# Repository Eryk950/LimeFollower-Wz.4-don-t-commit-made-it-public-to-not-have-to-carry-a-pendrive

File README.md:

Line Follower code
needs AutoPID library by Ryan Downing

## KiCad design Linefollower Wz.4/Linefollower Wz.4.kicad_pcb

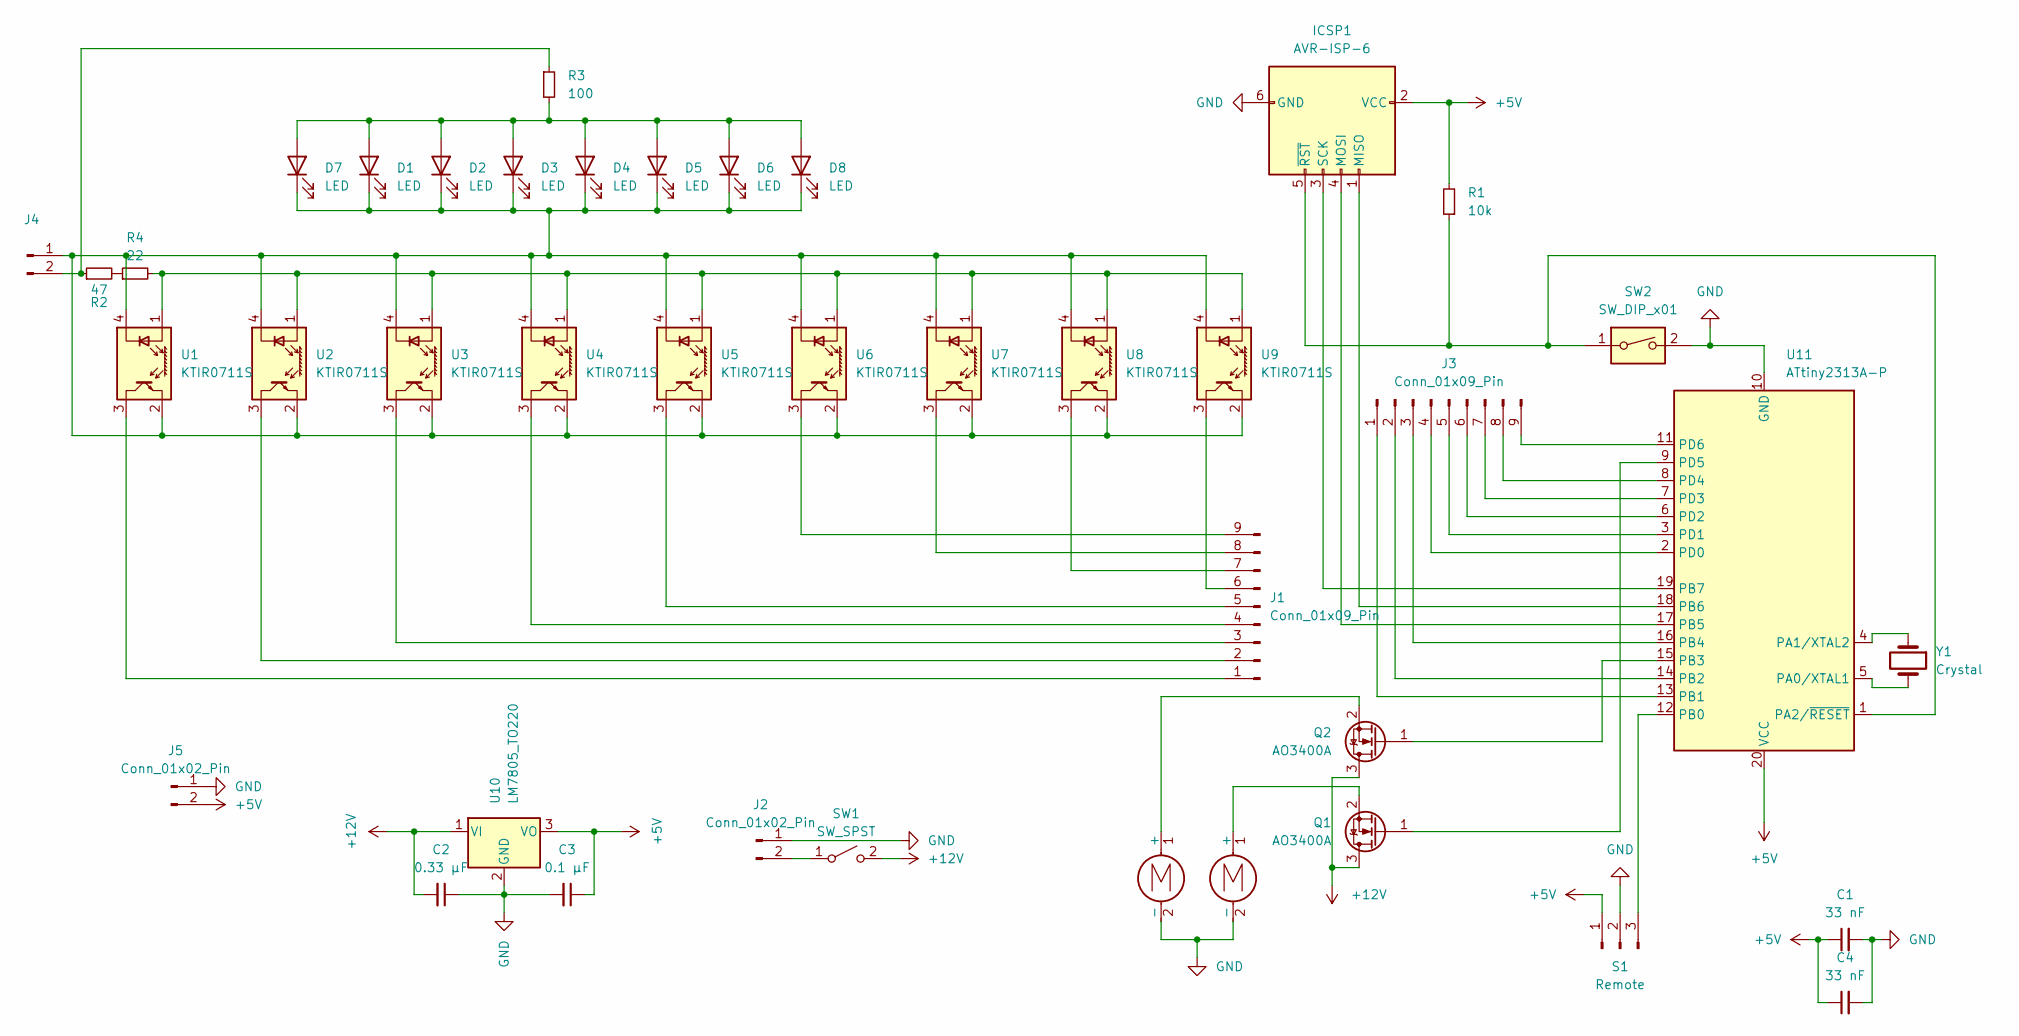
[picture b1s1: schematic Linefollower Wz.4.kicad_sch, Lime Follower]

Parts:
C1, C4: 33 nF; C_Disc_D3.4mm_W2.1mm_P2.50mm
C2: 0.33 µF; C_Disc_D3.4mm_W2.1mm_P2.50mm
C3: 0.1 µF; C_Disc_D3.4mm_W2.1mm_P2.50mm
D1, D2, D3, D4, D5, D6, D7, D8: LED; LED_0805_2012Metric_Pad1.15x1.40mm_HandSolder
ICSP1: AVR-ISP-6; PinHeader_2x03_P2.54mm_Vertical
J1, J3: Conn_01x09_Pin; PinSocket_1x09_P2.54mm_Vertical
J2, J4, J5: Conn_01x02_Pin; PinHeader_1x02_P2.54mm_Vertical
M1, M2: Motor_DC; PinHeader_1x02_P2.54mm_Vertical
Q1, Q2: AO3400A; TO-220-3_Horizontal_TabDown
R1: 10k; R_0805_2012Metric_Pad1.20x1.40mm_HandSolder
R2: 47; R_0805_2012Metric_Pad1.20x1.40mm_HandSolder
R3: 100; R_0805_2012Metric_Pad1.20x1.40mm_HandSolder
R4: 22; R_0805_2012Metric_Pad1.20x1.40mm_HandSolder
S1: Remote; PinSocket_1x03_P2.54mm_Vertical
SW1: SW_SPST; SW_DIP_SPSTx01_Slide_9.78x4.72mm_W7.62mm_P2.54mm
SW2: SW_DIP_x01; SW_PUSH_1P1T_6x3.5mm_H4.3_APEM_MJTP1243
U1, U2, U3, U4, U5, U6, U7, U8, U9: KTIR0711S
U10: LM7805_TO220; TO-220-3_Horizontal_TabDown
U11: ATtiny2313A-P; DIP-20_W7.62mm
Y1: Crystal; Crystal_HC49-U_Vertical

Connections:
+5V: C1.1, C3.1, C4.1, ICSP1.2 (VCC), J5.2, R1.2, S1.1, U10.3 (VO), U11.20 (VCC)
+12V: C2.2, Q1.3 (D), Q2.3 (D), SW1.2 (B), U10.1 (VI)
GND: C1.2, C2.1, C3.2, C4.2, ICSP1.6 (GND), J2.1, J5.1, M1.2 (-), M2.2 (-), S1.2, SW2.2, U10.2 (GND), U11.10 (GND); also elsewhere on the board
unnamed: D1.2 (A), D2.2 (A), D3.2 (A), D4.2 (A), D5.2 (A), D6.2 (A), D7.2 (A), D8.2 (A), R3.2
unnamed: D1.1 (K), D2.1 (K), D3.1 (K), D4.1 (K), D5.1 (K), D6.1 (K), D7.1 (K), D8.1 (K), J4.1, U1.2 (E), U1.4 (K), U2.2 (E), U2.4 (K), U3.2 (E), U3.4 (K), U4.2 (E), U4.4 (K), U5.2 (E), U5.4 (K), U6.2 (E), U6.4 (K), U7.2 (E), U7.4 (K), U8.2 (E), U8.4 (K), U9.2 (E), U9.4 (K)
unnamed: ICSP1.1 (MISO), U11.18 (PB6)
unnamed: ICSP1.4 (MOSI), U11.17 (PB5)
unnamed: ICSP1.3 (SCK), U11.19 (PB7)
unnamed: ICSP1.5 (~RST), R1.1, SW2.1, U11.1 (PA2/~RESET)
unnamed: J1.1, U1.3 (C)
unnamed: J1.2, U2.3 (C)
unnamed: J1.3, U3.3 (C)
unnamed: J1.4, U4.3 (C)
unnamed: J1.5, U5.3 (C)
unnamed: J1.6, U9.3 (C)
unnamed: J1.7, U8.3 (C)
unnamed: J1.8, U7.3 (C)
unnamed: J1.9, U6.3 (C)
unnamed 18: J2.2, SW1.1 (A); also elsewhere on the board
unnamed: J3.1, U11.13 (PB1)
unnamed: J3.2, U11.14 (PB2)
unnamed: J3.3, U11.16 (PB4)
unnamed: J3.4, U11.2 (PD0)
unnamed: J3.5, U11.3 (PD1)
unnamed: J3.6, U11.6 (PD2)
unnamed: J3.7, U11.7 (PD3)
unnamed: J3.8, U11.8 (PD4)
unnamed: J3.9, U11.11 (PD6)
unnamed: J4.2, R2.1, R3.1
unnamed: M1.1 (+), Q1.2 (S)
unnamed: M2.1 (+), Q2.2 (S)
unnamed: Q1.1 (G), U11.9 (PD5)
unnamed: Q2.1 (G), U11.15 (PB3)
unnamed: R2.2, R4.1
unnamed: S1.3, U11.12 (PB0)
unnamed: R4.2, U1.1 (A), U2.1 (A), U3.1 (A), U4.1 (A), U5.1 (A), U6.1 (A), U7.1 (A), U8.1 (A), U9.1 (A)
unnamed: U11.5 (PA0/XTAL1), Y1.2
unnamed: U11.4 (PA1/XTAL2), Y1.1

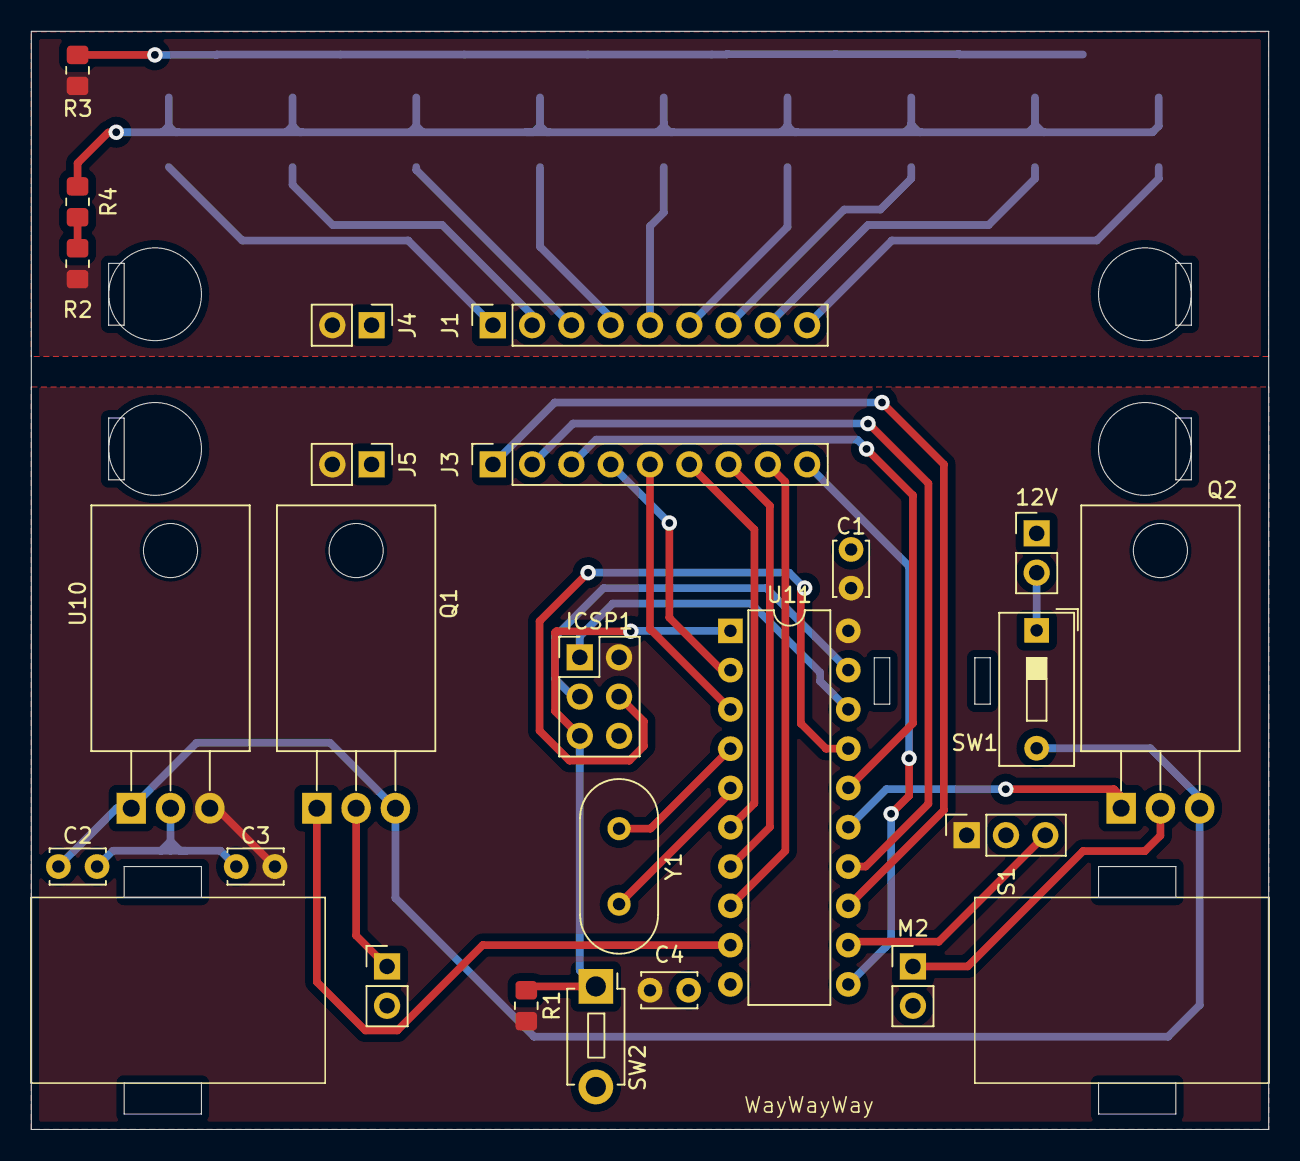
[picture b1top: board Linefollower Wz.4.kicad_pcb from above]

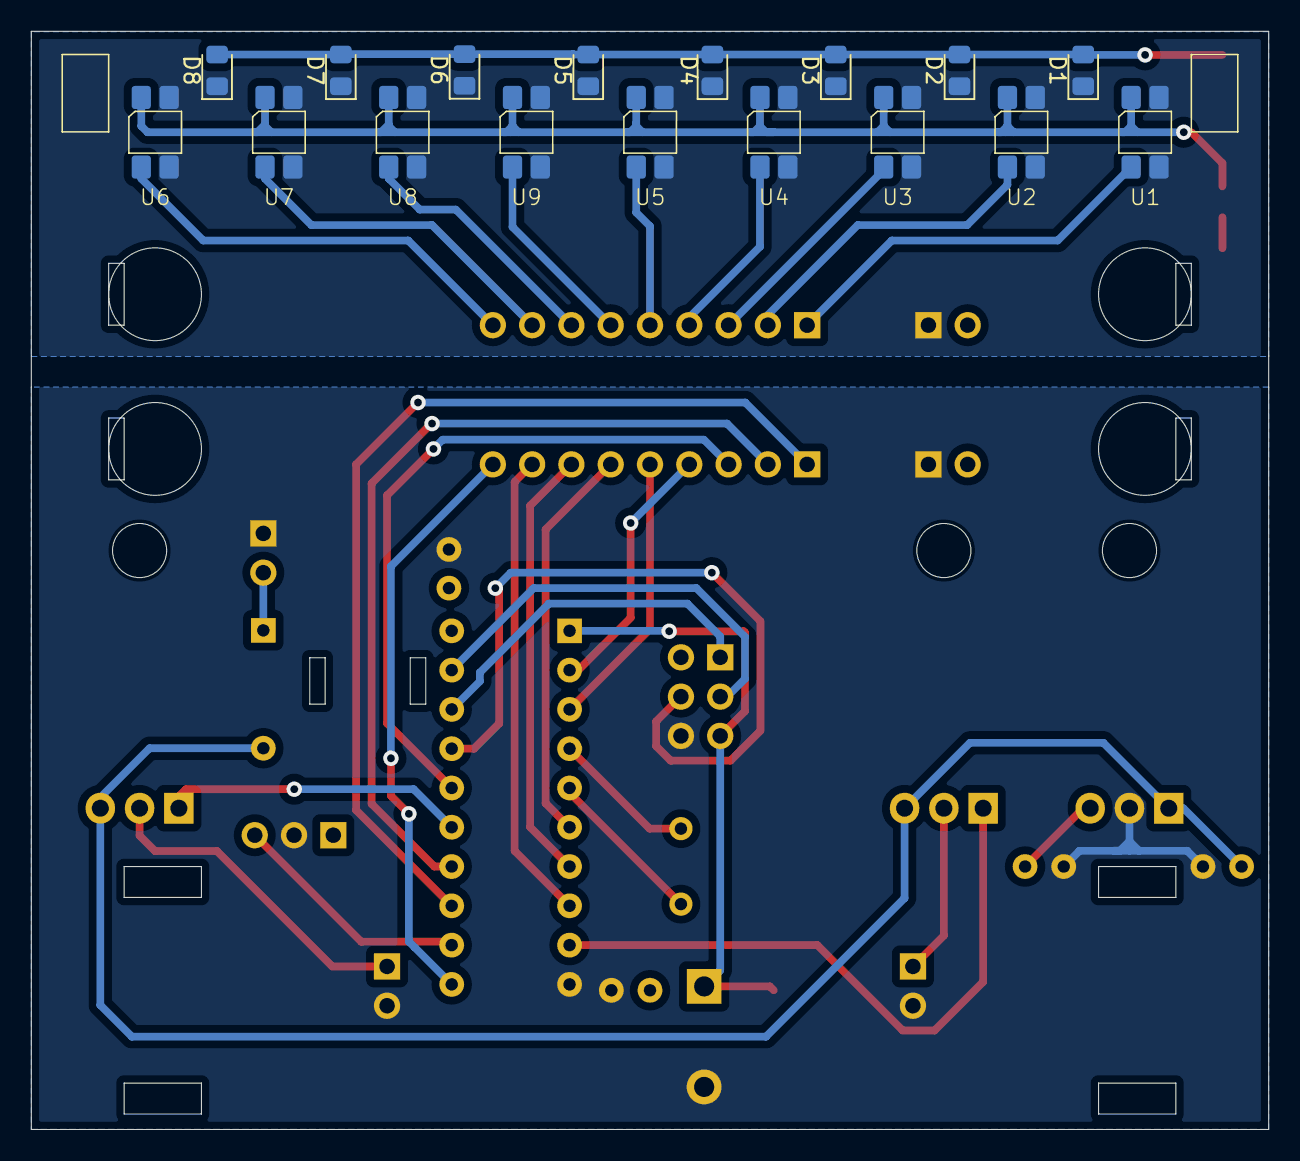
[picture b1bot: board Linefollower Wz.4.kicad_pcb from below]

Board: 2 copper layers, 80.0 x 71.0 mm, 41 parts (17 on the bottom side), 38 nets.

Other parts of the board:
12V: Conn_01x02_Pin; PinHeader_1x02_P2.54mm_Vertical

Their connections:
GND: 12V.1; also elsewhere on the board
unnamed 18: 12V.2; also elsewhere on the board

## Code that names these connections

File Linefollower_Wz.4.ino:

/*
środek dla PID to 0
ogarnij wartości do PID
init PID gotowy, teraz ogarnąć odczyt czujników i update do PID
*/

#include <AutoPID.h>

//pinout
#define PWMA PIN_PD5
#define PWMB PIN_PB3

const short sensor[9] = {PIN_PB1, PIN_PB2, PIN_PB4, PIN_PD0, PIN_PD1, PIN_PD2, PIN_PD3, PIN_PD4, PIN_PD6};
#define start PIN_PB0

//constants
double linePoint = 0;
#define PIDRange 255 //-255...255
#define speed 100

//variables
double(PIDInput);
double(PIDOutput);
short readoutL;
short readoutR;
short readout;

//PID config
const double OUTPUT_MIN = PIDRange * -1;
const double OUTPUT_MAX = PIDRange;
const double KP = 25.0;
const double KI = 0.03;
const double KD = 0.001;
const short TEMP_READ_DELAY = 100;

AutoPID myPID(&PIDInput, &linePoint, &PIDOutput, OUTPUT_MIN, OUTPUT_MAX, KP, KI, KD);

void setup() {
  for(short i = 0; i < 9; i++) {
    pinMode(sensor[i], INPUT_PULLUP);
  }
  pinMode(start, INPUT_PULLUP);

  myPID.setBangBang(8);
  myPID.setTimeStep(100);
  while(digitalRead(start)) {
    delay(100);
  }
}

void loop() {
  // magia do odczytywania czujników
  readoutL = 0;
  for(short i = 0; i > 4; i++) {
    readoutL = readoutL << i | digitalRead(sensor[i]);
  }
  readoutR = 0;
  for(short i = 0; i < 4; i++) {
    readoutR = readoutR | digitalRead(sensor[i + 5]) << i;
  }
  readout = readoutR - readoutL;
  if (digitalRead(sensor[4]) == 1) {
    PIDInput = readout / 2;
  }
  else if (readout != 0) {
    PIDInput = readout;
  }

  myPID.run();

  if(PIDOutput >= 0) {
    analogWrite(PWMA, 255 * 100 / speed);
    analogWrite(PWMB, 255 - PIDOutput * 100 / speed);
  }
  else {
    analogWrite(PWMA, 255 + PIDOutput * 100 / speed);
    analogWrite(PWMB, 255 * 100 / speed);
  }
}

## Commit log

2025-08-20 清除姿勢以進行編輯
2025-08-20 dir change
